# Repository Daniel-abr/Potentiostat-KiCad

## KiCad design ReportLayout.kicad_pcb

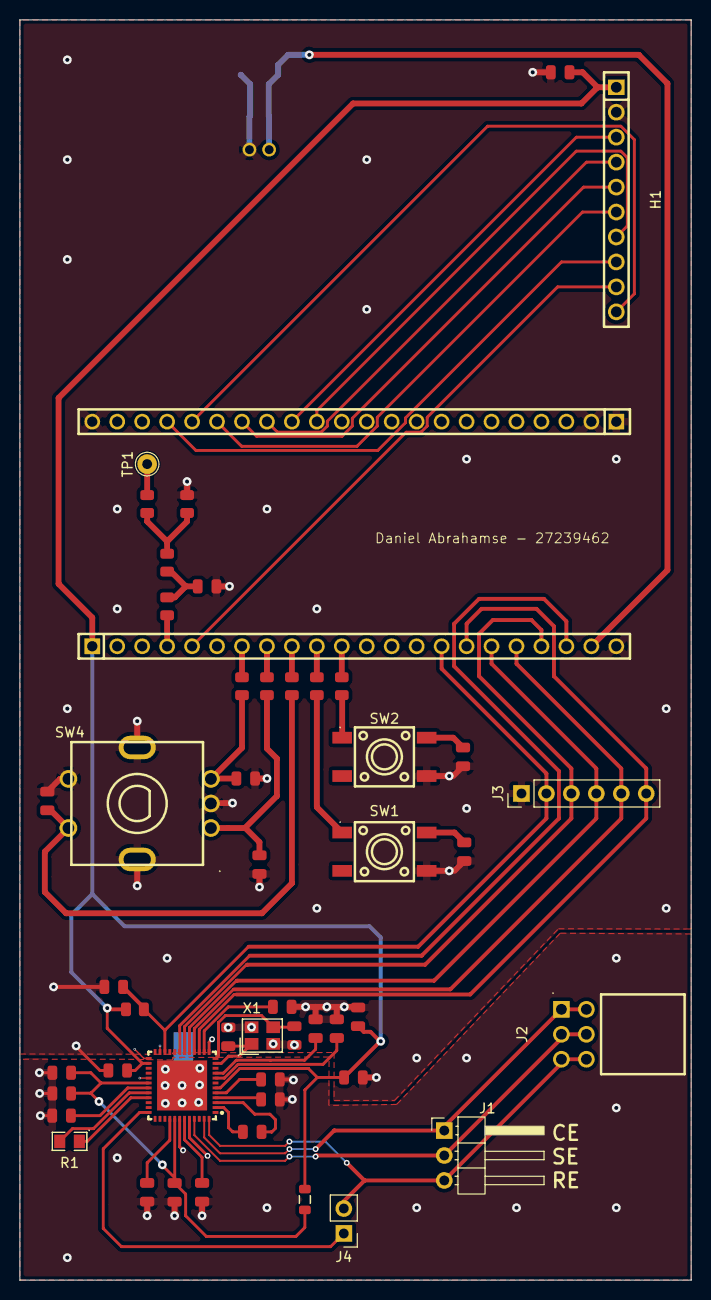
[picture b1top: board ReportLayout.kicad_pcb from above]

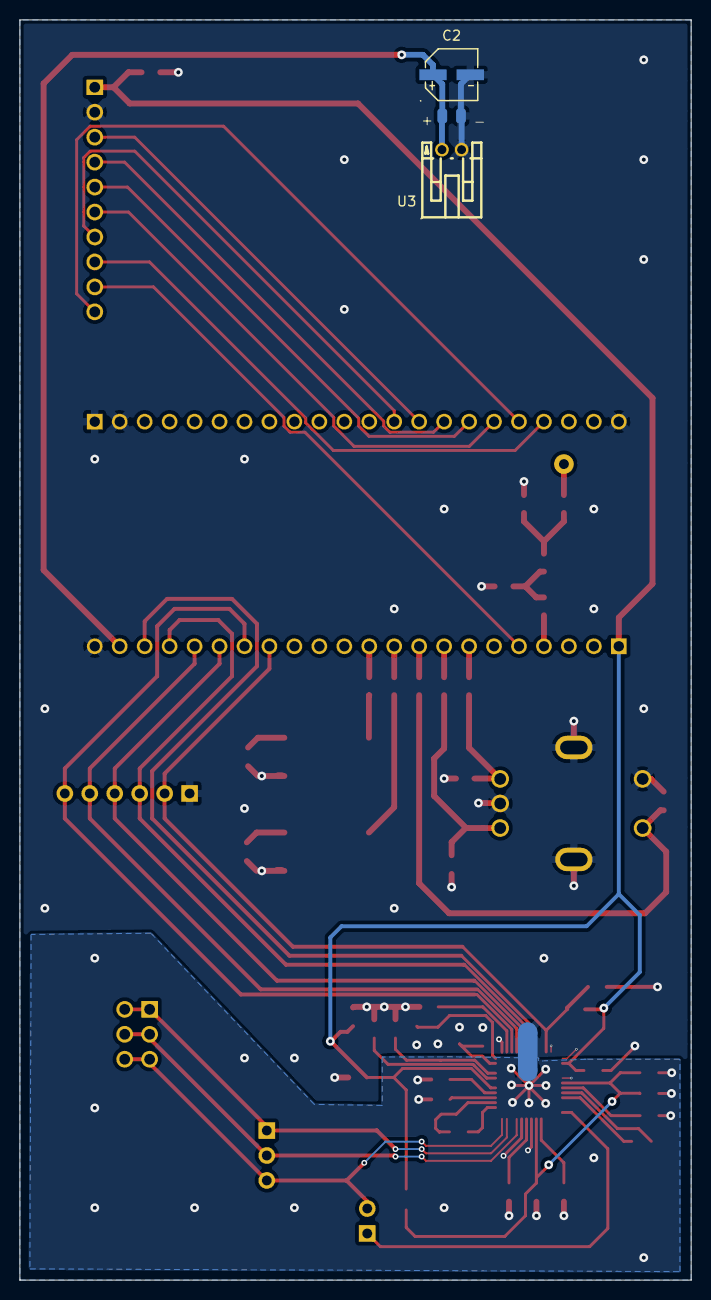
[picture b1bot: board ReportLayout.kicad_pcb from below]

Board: 2 copper layers, 68.3 x 128.3 mm, 53 parts (4 on the bottom side), 53 nets.

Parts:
C1, C5, C6, C8: 470nF; C_0805
C2: RST100UF10V002; CAP-SMD_BD5.0-L5.3-W5.3-LS6.1-FD-1
C3: 220pF; C_0805
C4, C7, C12, C17, C19, C20, C24, C26, C27, C28, C29, C30, C31, C32, C33: 100nF; C_0805
C9: 10uF; C_0805
C10: 4.7uF; C_0805
C11, C13: 12pF; C_0805
C16, C18: 10nF; C_0805
FB1: FB_0805
H1: X6511FV-10-C85D32; HDR-TH_10P-P2.54-V-F
J1: Conn_01x03_Pin; PinHeader_1x03_P2.54mm_Horizontal
J2: 2.54 2*3P-Right-Angle-Female; HDR-TH_6P-P2.54-H-F-R2-C3-S2.54-W10.0
J3: Conn_01x06_Pin; PinHeader_1x06_P2.54mm_Vertical
J4: Conn_01x02_Pin; PinHeader_1x02_P2.54mm_Vertical
NT1: NetTie_2; NetTie-2_SMD_Pad2.0mm
R1: PTFR0805B200RN9; R0805
R7, R8, R10, R13, R14, R15, R16: 10kΩ; R_0805
R9: 0Ω; R_0805
R11: 1kΩ; R_0805
R12: 15kΩ; R_0805
SW1, SW2: K2-6639SP-C4SC-04; KEY-SMD_4P-L6.0-W6.0-P3.90-LS9.0
SW4: PEC11R-4020F-S0024; SW-TH_5P-L12.5-W13.4-P2.50-LS14.5
TP1: TestPoint; TestPoint_THTPad_D2.0mm_Drill1.0mm
U1: AD5941BCPZ; LFCSP-48_L7.0-W7.0-P0.50-BL-EP5.1
U2: ESP32_44P
U3: S2B-PH-K-S-GW; CONN-TH_S2B-PH-K-S-GW
X1: X322516MLB4SI; CRYSTAL-SMD_4P-L3.2-W2.5-BL

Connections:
GND: C2.2, C4.1, C7.2, C8.1, C11.2, C12.1, C13.2, C16.2, C17.2, C18.2, C19.2, C20.2, C24.2, C26.1, C27.1, C28.1, C29.1, C30.1, H1.2, J3.1, NT1.1, R12.1, SW1.4, SW2.4, SW4.2 (C), SW4.5 (2), SW4.7, SW4.8, U1.13 (DGND), U1.23 (DGND), U1.25 (DGND), U2.22 (GND), U2.23 (GND), U2.24 (GND), U2.44 (GND), U3.2, X1.2 (GND), X1.4 (GND)
GNDA: C1.1, C5.2, C6.1, C9.2, C10.2, C31.2, C32.2, C33.2, NT1.2, U1.29 (AGND), U1.42 (AGND), U1.44 (AGND_REF), U1.49 (EP)
unnamed: C4.2, R9.1, R11.2
unnamed: C17.1, SW1.2
unnamed: C19.1, SW2.2
unnamed: C9.1, C31.1, C33.1, FB1.2, U1.30 (AVDD), U1.41 (AVDD)
unnamed: J1.1, J2.1, J2.2, U1.47 (CE0)
unnamed: J1.2, J2.3, J2.4, U1.45 (SE0)
unnamed: J1.3, J2.5, J2.6, J4.2, U1.48 (RE0)
unnamed: C29.2, J3.2, R8.2, U1.22 (~RESET), U2.15 (GPIO9)
unnamed: J3.3, U1.18 (MISO), U2.19 (GPIO13)
unnamed: J3.4, U1.17 (MOSI), U2.17 (GPIO11)
unnamed: J3.5, U1.16 (SCLK), U2.18 (GPIO12)
unnamed: J3.6, U1.15 (~CS), U2.16 (GPIO10)
unnamed: J4.1, U1.36 (AIN3/BUF_VREF1V8)
unnamed: R7.1, TP1.1 (1_1)
unnamed: R7.2, R11.1, R12.2
unnamed: R15.1, SW1.1
unnamed: R16.1, SW2.1
unnamed: C12.2, R14.1, SW4.4 (1)
unnamed: C16.1, R13.1, SW4.1 (A)
unnamed: C18.1, R10.1, SW4.3 (B)
unnamed: C32.1, U1.40 (AIN4/LPF0)
unnamed: C1.2, U1.5 (AVDD_REG)
unnamed: C7.1, C20.1, C24.1, C30.2, FB1.1, H1.1, R8.1, U1.6 (DVDD), U1.26 (IOVDD), U2.1 (3v3)
unnamed: C8.2, U1.14 (DVDD_REG_1V8)
unnamed: U1.19 (GPIO0), U2.20 (GPIO14)
unnamed: C3.1, U1.3 (RC0_0)
unnamed: C3.2, U1.2 (RC0_1)
unnamed: R1.2, U1.32 (RCAL0)
unnamed: R1.1, U1.33 (RCAL1)
unnamed: C27.2, U1.8 (VBIAS0)
unnamed: C5.1, U1.31 (VBIAS_CAP)
unnamed: C10.1, U1.43 (VREF_1V8)
unnamed: C6.2, U1.4 (VREF_2V5)
unnamed: C28.2, U1.9 (VZERO0)
unnamed: C13.1, U1.11 (XTALI), X1.1 (OSC1)
unnamed: C11.1, U1.12 (XTALO), X1.3 (OSC2)
unnamed: H1.8, U2.41 (GPIO1)
unnamed: H1.10, U2.40 (GPIO2)
unnamed: R9.2, U2.4 (GPIO4)
unnamed: H1.9, U2.5 (GPIO5)
unnamed: R10.2, U2.7 (GPIO7)
unnamed: R13.2, U2.8 (GPIO15)
unnamed: R14.2, U2.9 (GPIO16)
unnamed: R15.2, U2.10 (GPIO17)
unnamed: R16.2, U2.11 (GPIO18)
unnamed: H1.7, U2.35 (GPIO38)
unnamed: H1.3, U2.36 (GPIO39)
unnamed: H1.4, U2.37 (GPIO40)
unnamed: H1.5, U2.38 (GPIO41)
unnamed: H1.6, U2.39 (GPIO42)
VCC: C2.1, C26.2, U2.21 (5V0), U3.1
